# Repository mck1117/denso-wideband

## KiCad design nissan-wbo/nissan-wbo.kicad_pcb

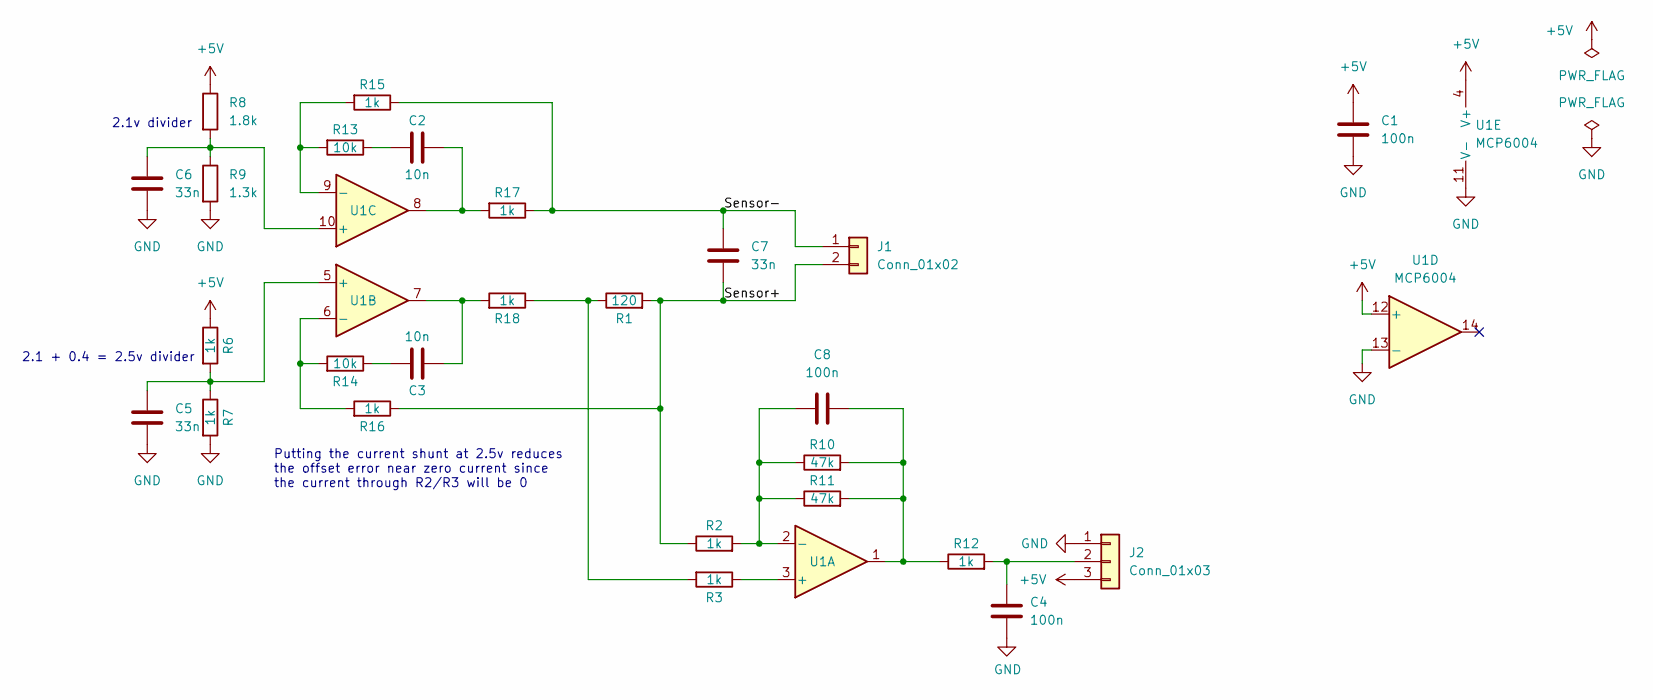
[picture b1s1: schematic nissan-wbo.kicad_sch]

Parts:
C1, C4, C8: 100n; C_0603_1608Metric; LCSC C57112
C2, C3: 10n; C_0402_1005Metric; LCSC C15195
C5, C6, C7: 33n; C_0402_1005Metric; LCSC C1585
J1: Conn_01x02; SolderWire-0.75sqmm_1x02_P4.8mm_D1.25mm_OD2.3mm
J2: Conn_01x03; SolderWire-0.75sqmm_1x03_P4.8mm_D1.25mm_OD2.3mm
R1: 120; R_0402_1005Metric; LCSC C25079
R2, R3, R6, R7, R12, R15, R16, R17, R18: 1k; R_0402_1005Metric; LCSC C11702
R8: 1.8k; R_0603_1608Metric; LCSC C4177
R9: 1.3k; R_0402_1005Metric; LCSC C227316
R10, R11: 47k; R_0402_1005Metric; LCSC C25792
R13, R14: 10k; R_0402_1005Metric; LCSC C25744
U1: MCP6004; TSSOP-14_4.4x5mm_P0.65mm; LCSC C50282

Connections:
+5V: C1.1, J2.3, R6.1, R8.1, U1.4 (V+), U1.12 (+)
/Sensor+: C7.1, J1.2, R1.2, R2.1, R16.1
/Sensor-: C7.2, J1.1, R15.1, R17.1
GND: C1.2, C4.1, C5.2, C6.2, J2.1, R7.2, R9.2, U1.11 (V-), U1.13 (-)
unnamed: C2.1, R13.1
unnamed: C2.2, R17.2, U1.8
unnamed: C3.1, R14.1
unnamed: C3.2, R18.2, U1.7
unnamed: C4.2, J2.2, R12.2
unnamed: C5.1, R6.2, R7.1, U1.5 (+)
unnamed: C6.1, R8.2, R9.1, U1.10 (+)
unnamed: C8.1, R2.2, R10.1, R11.1, U1.2 (-)
unnamed: C8.2, R10.2, R11.2, R12.1, U1.1
unnamed: R1.1, R3.2, R18.1
unnamed: R3.1, U1.3 (+)
unnamed: R13.2, R15.2, U1.9 (-)
unnamed: R14.2, R16.2, U1.6 (-)

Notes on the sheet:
2.1v divider
2.1 + 0.4 = 2.5v divider
Putting the current shunt at 2.5v reduces the offset error near zero current since the current through R2/R3 will be 0

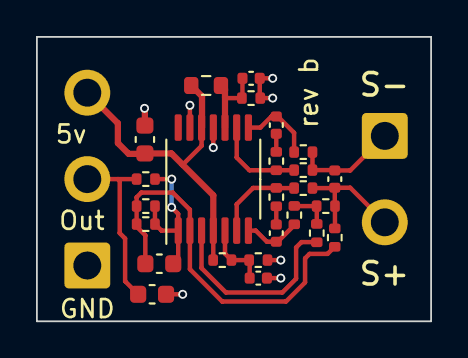
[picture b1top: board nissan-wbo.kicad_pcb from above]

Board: 2 copper layers, 21.9 x 15.8 mm, 27 parts (0 on the bottom side), 17 nets.

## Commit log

2022-12-03 gitignore
2022-12-03 hardware
2022-12-03 sim gitignore
2022-12-03 ltspice model
2022-12-03 LCSC
2022-12-10 add via (C4, GND) and export gerbers
2022-12-12 rename columns
2023-02-02 fix silk
